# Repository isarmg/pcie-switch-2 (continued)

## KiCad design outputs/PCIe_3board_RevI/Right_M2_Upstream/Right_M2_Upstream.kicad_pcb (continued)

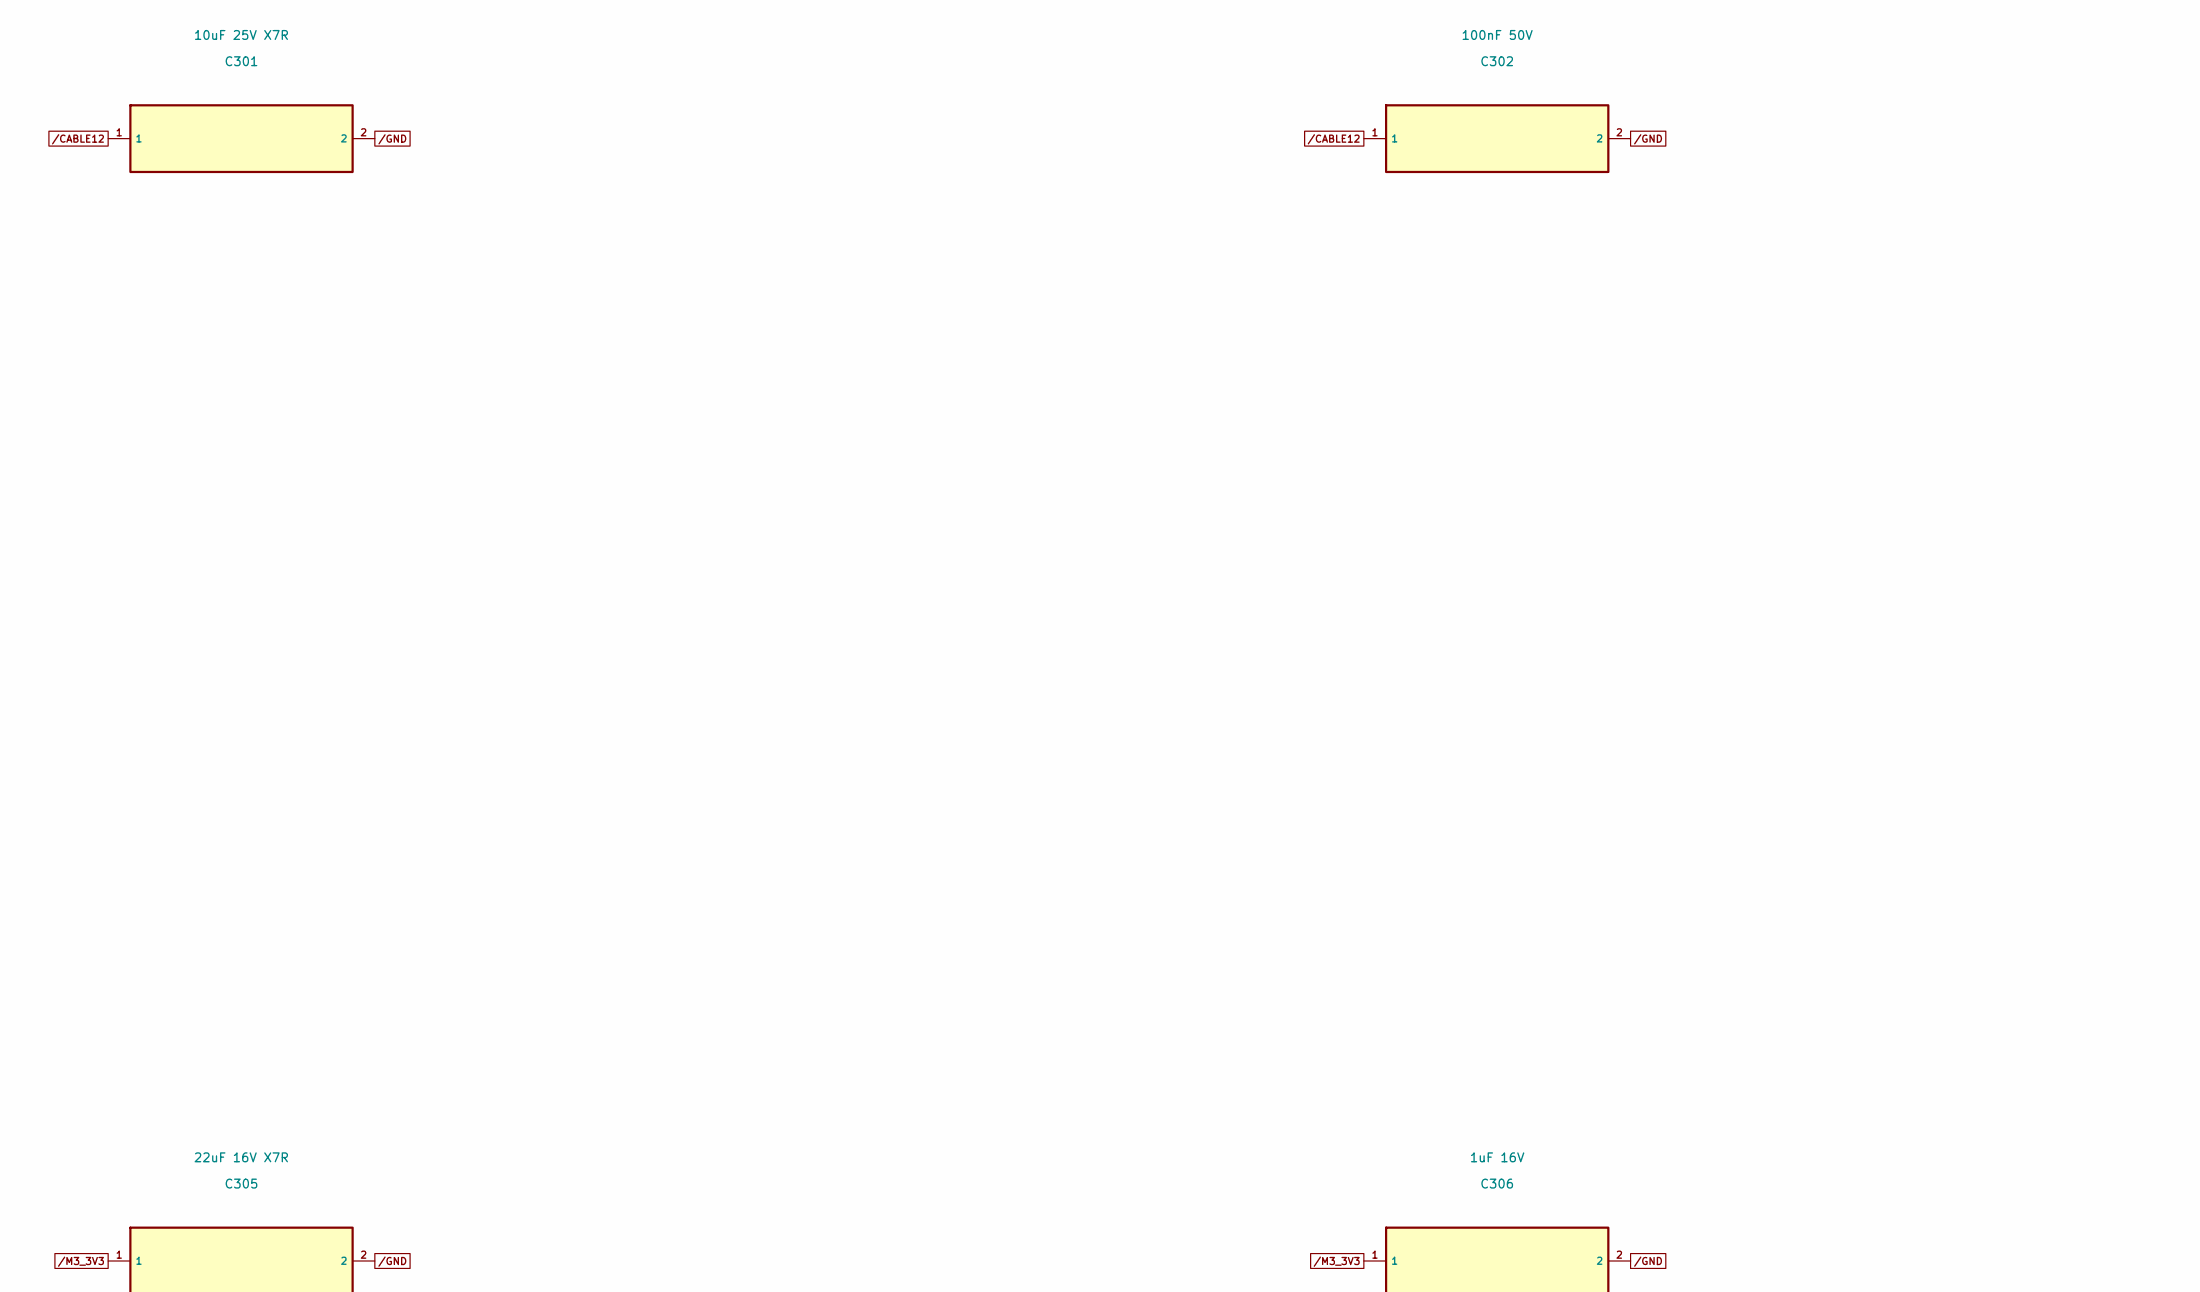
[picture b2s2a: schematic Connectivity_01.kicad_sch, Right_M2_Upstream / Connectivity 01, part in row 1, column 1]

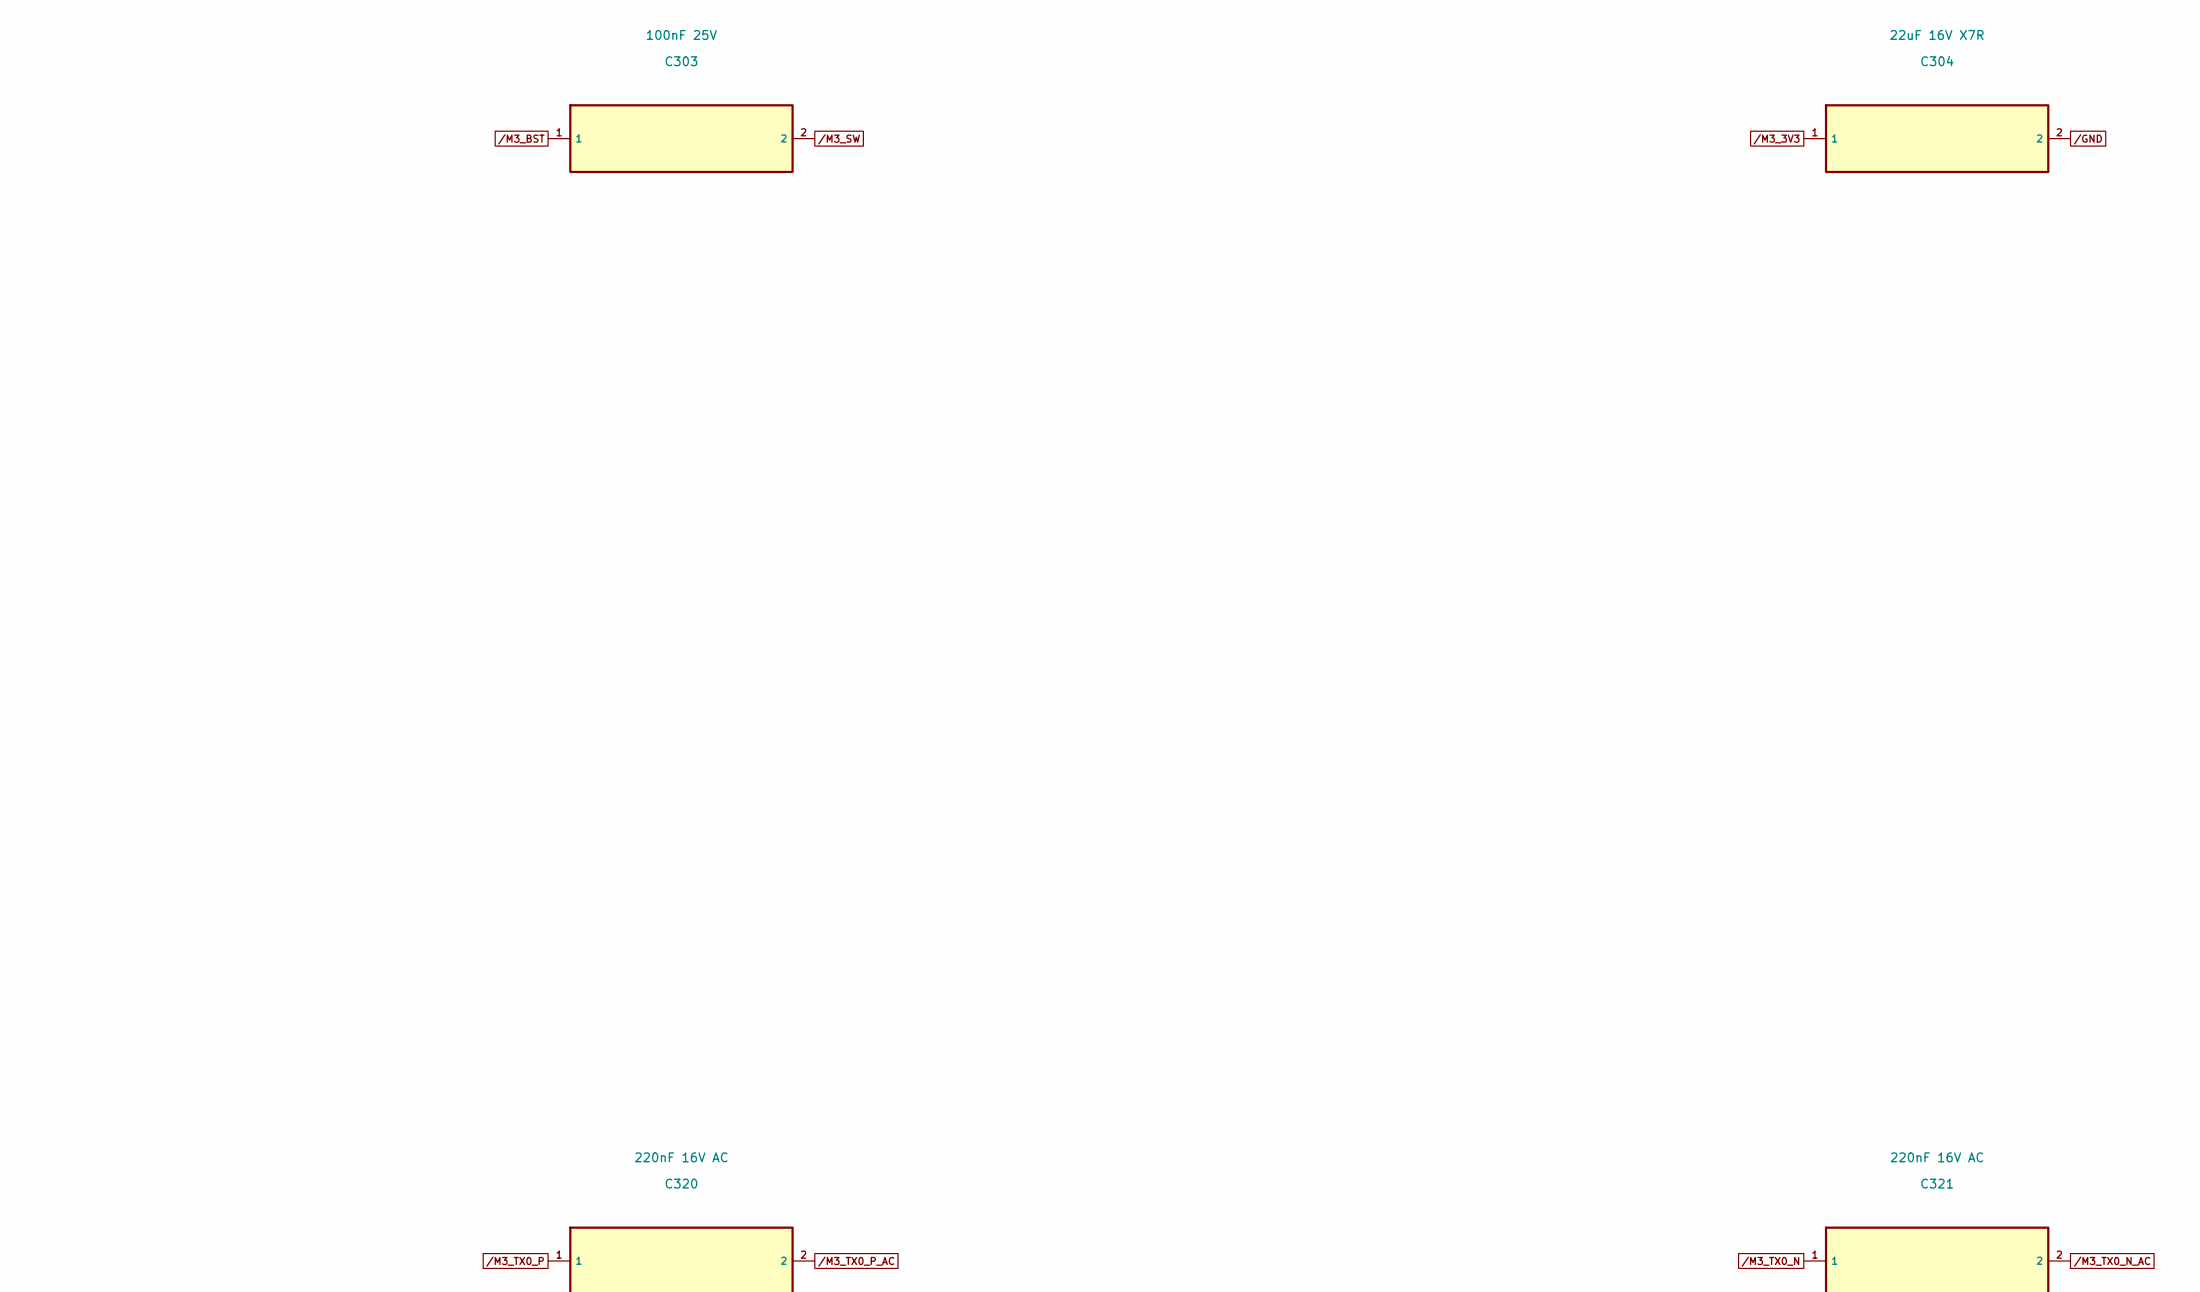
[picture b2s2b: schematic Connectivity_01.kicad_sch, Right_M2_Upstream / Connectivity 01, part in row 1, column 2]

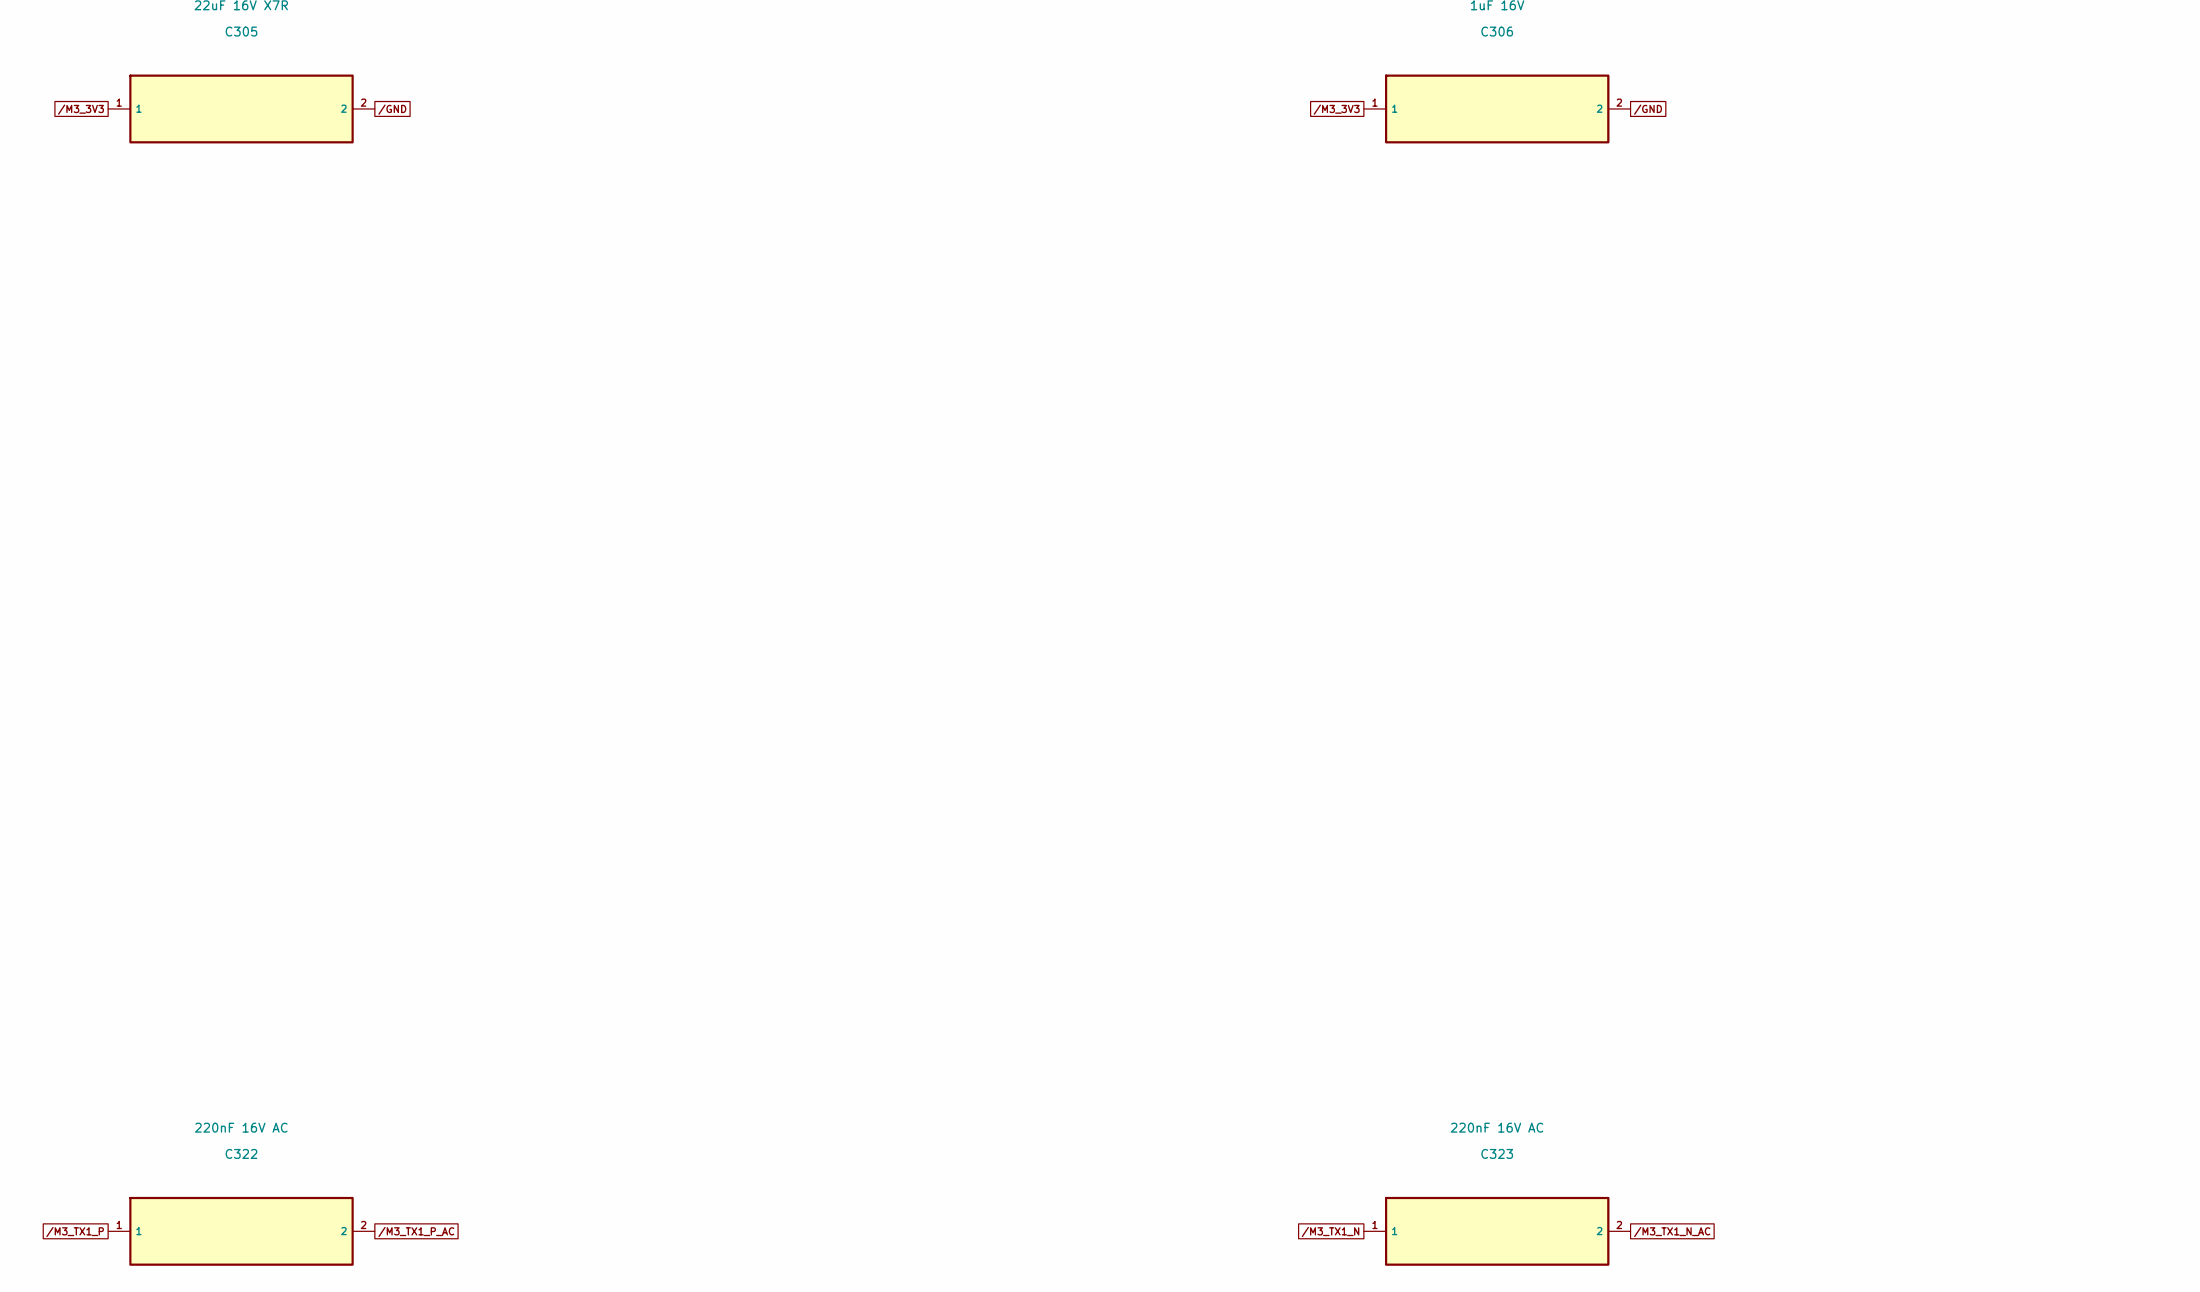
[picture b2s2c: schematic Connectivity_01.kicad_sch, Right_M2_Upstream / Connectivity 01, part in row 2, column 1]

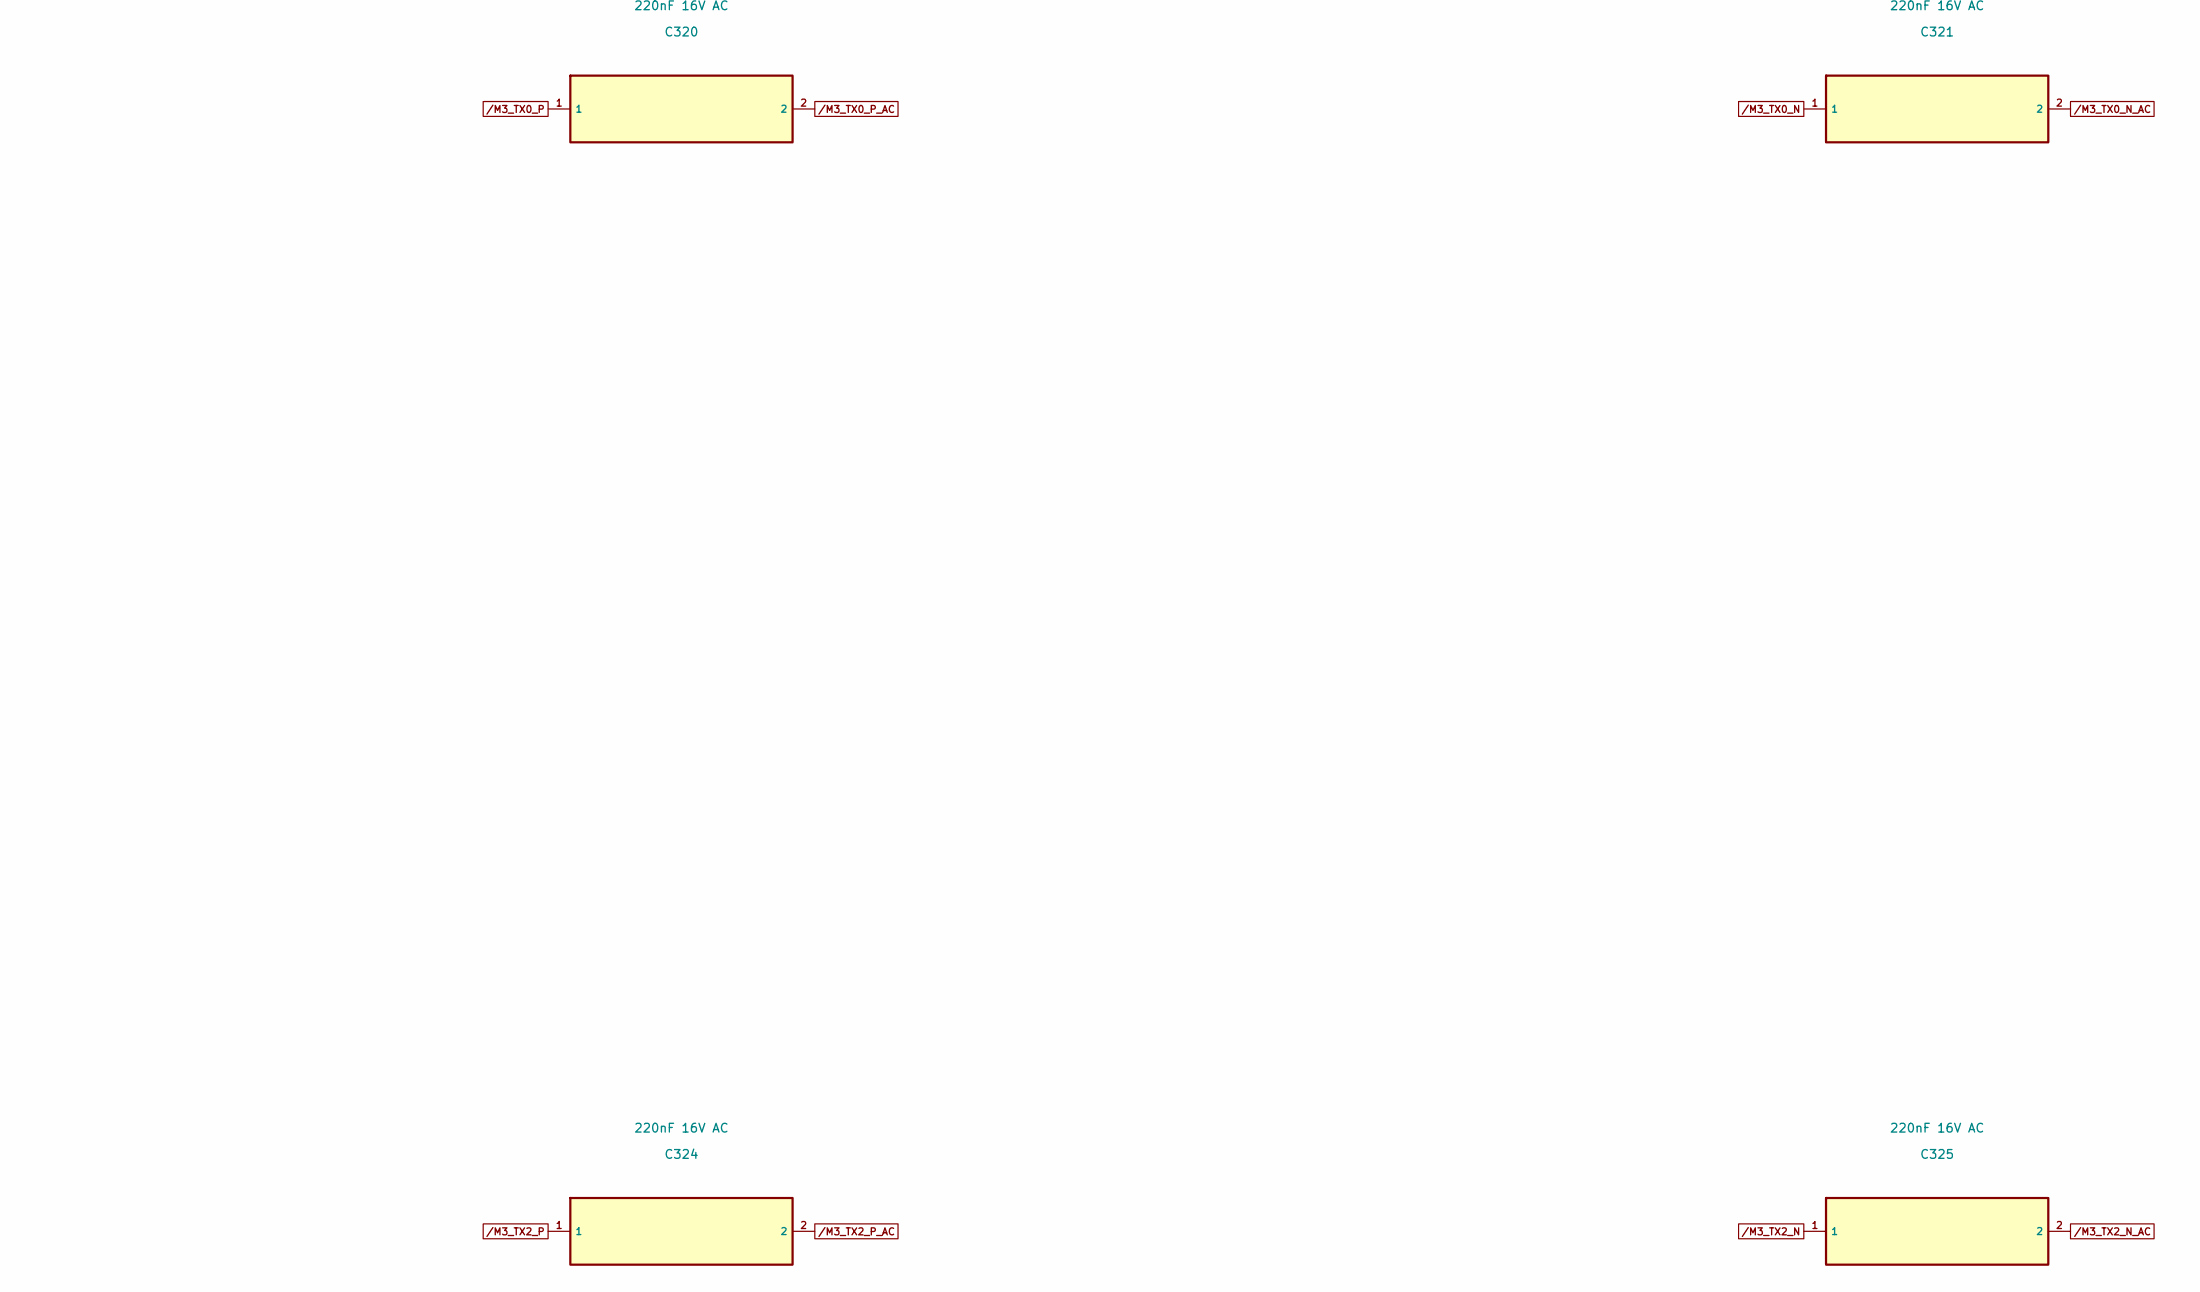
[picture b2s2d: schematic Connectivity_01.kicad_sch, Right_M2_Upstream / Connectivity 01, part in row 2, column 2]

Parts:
C301: 10uF 25V X7R; C_0805_2012Metric
C302: 100nF 50V; C_0402_1005Metric
C303: 100nF 25V; C_0402_1005Metric
C304, C305: 22uF 16V X7R; C_1210_3225Metric
C306: 1uF 16V; C_0603_1608Metric
C320, C321, C322, C323, C324, C325: 220nF 16V AC; C_0402_1005Metric

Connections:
/CABLE12: C301.1, C302.1; also elsewhere on the board
/GND: C301.2, C302.2, C304.2, C305.2, C306.2; also elsewhere on the board
/M3_3V3: C304.1, C305.1, C306.1; also elsewhere on the board
/M3_BST: C303.1; also elsewhere on the board
/M3_SW: C303.2; also elsewhere on the board
/M3_TX0_N: C321.1; also elsewhere on the board
/M3_TX0_N_AC: C321.2; also elsewhere on the board
/M3_TX0_P: C320.1; also elsewhere on the board
/M3_TX0_P_AC: C320.2; also elsewhere on the board
/M3_TX1_N: C323.1; also elsewhere on the board
/M3_TX1_N_AC: C323.2; also elsewhere on the board
/M3_TX1_P: C322.1; also elsewhere on the board
/M3_TX1_P_AC: C322.2; also elsewhere on the board
/M3_TX2_N: C325.1; also elsewhere on the board
/M3_TX2_N_AC: C325.2; also elsewhere on the board
/M3_TX2_P: C324.1; also elsewhere on the board
/M3_TX2_P_AC: C324.2; also elsewhere on the board

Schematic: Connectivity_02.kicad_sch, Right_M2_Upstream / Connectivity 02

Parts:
C326, C327, C420, C421, C422, C423, C424, C425, C426, C427: 220nF 16V AC; C_0402_1005Metric
J3: M-Key 2280 VERTICAL / LAND DRAFT; M2_MKey_VERTICAL_5p3_DRAFT

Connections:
/GND: J3.1 (GND), J3.3 (GND), J3.9 (GND), J3.15 (GND), J3.21 (GND), J3.27 (GND), J3.33 (GND), J3.39 (GND), J3.45 (GND), J3.51 (GND), J3.57 (GND), J3.69 (PEDET), J3.71 (GND), J3.73 (GND), J3.75 (GND), J3.MP1, J3.MP2; also elsewhere on the board
/M3_3V3: J3.2 (3.3V), J3.4 (3.3V), J3.12 (3.3V), J3.14 (3.3V), J3.16 (3.3V), J3.18 (3.3V), J3.70 (3.3V), J3.72 (3.3V), J3.74 (3.3V); also elsewhere on the board
/M3_CLKREQ: J3.52 (~CLKREQ); also elsewhere on the board
/M3_CLK_N: J3.53 (REFCLKn); also elsewhere on the board
/M3_CLK_P: J3.55 (REFCLKp); also elsewhere on the board
/M3_PERST: J3.50 (~PERST); also elsewhere on the board
/M3_RX0_N: J3.41 (PERn0/SATA-B+); also elsewhere on the board
/M3_RX0_P: J3.43 (PERp0/SATA-B-); also elsewhere on the board
/M3_RX1_N: J3.29 (PERn1); also elsewhere on the board
/M3_RX1_P: J3.31 (PERp1); also elsewhere on the board
/M3_RX2_N: J3.17 (PERn2); also elsewhere on the board
/M3_RX2_P: J3.19 (PERp2); also elsewhere on the board
/M3_RX3_N: J3.5 (PERn3); also elsewhere on the board
/M3_RX3_P: J3.7 (PERp3); also elsewhere on the board
/M3_TX0_N_AC: J3.47 (PETn0/SATA-A-); also elsewhere on the board
/M3_TX0_P_AC: J3.49 (PETp0/SATA-A+); also elsewhere on the board
/M3_TX1_N_AC: J3.35 (PETn1); also elsewhere on the board
/M3_TX1_P_AC: J3.37 (PETp1); also elsewhere on the board
/M3_TX2_N_AC: J3.23 (PETn2); also elsewhere on the board
/M3_TX2_P_AC: J3.25 (PETp2); also elsewhere on the board
/M3_TX3_N: C327.1; also elsewhere on the board
/M3_TX3_N_AC: C327.2, J3.11 (PETn3)
/M3_TX3_P: C326.1; also elsewhere on the board
/M3_TX3_P_AC: C326.2, J3.13 (PETp3)
/M3_WAKE: J3.54 (~PEWAKE); also elsewhere on the board
/UP_TX0_N: C421.1; also elsewhere on the board
/UP_TX0_N_AC: C421.2; also elsewhere on the board
/UP_TX0_P: C420.1; also elsewhere on the board
/UP_TX0_P_AC: C420.2; also elsewhere on the board
/UP_TX1_N: C423.1; also elsewhere on the board
/UP_TX1_N_AC: C423.2; also elsewhere on the board
/UP_TX1_P: C422.1; also elsewhere on the board
/UP_TX1_P_AC: C422.2; also elsewhere on the board
/UP_TX2_N: C425.1; also elsewhere on the board
/UP_TX2_N_AC: C425.2; also elsewhere on the board
/UP_TX2_P: C424.1; also elsewhere on the board
/UP_TX2_P_AC: C424.2; also elsewhere on the board
/UP_TX3_N: C427.1; also elsewhere on the board
/UP_TX3_N_AC: C427.2; also elsewhere on the board
/UP_TX3_P: C426.1; also elsewhere on the board
/UP_TX3_P_AC: C426.2; also elsewhere on the board

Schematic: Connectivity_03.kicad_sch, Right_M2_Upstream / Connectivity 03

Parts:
J4: UPLINK M-Key / HOST ONLY; M2_MKey_VERTICAL_5p3_DRAFT
J50: 12V protected / GND; Wire_12V_GND_3A
J51: Control / custom; Control_8_Wire
J101: M3 TX0; Twinax_85R_Solder_DRAFT
J102: M3 RX0; Twinax_85R_Solder_DRAFT
J103: M3 TX1; Twinax_85R_Solder_DRAFT
J104: M3 RX1; Twinax_85R_Solder_DRAFT
J105: M3 TX2; Twinax_85R_Solder_DRAFT
J106: M3 RX2; Twinax_85R_Solder_DRAFT
J107: M3 TX3; Twinax_85R_Solder_DRAFT
J108: M3 RX3; Twinax_85R_Solder_DRAFT

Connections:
/CABLE12: J50.1; also elsewhere on the board
/GND: J4.1 (GND), J4.3 (GND), J4.9 (GND), J4.15 (GND), J4.21 (GND), J4.27 (GND), J4.33 (GND), J4.39 (GND), J4.45 (GND), J4.51 (GND), J4.57 (GND), J4.69 (PEDET), J4.71 (GND), J4.73 (GND), J4.75 (GND), J4.MP1, J4.MP2, J50.2, J51.7, J51.8, J101.G, J102.G, J103.G, J104.G, J105.G, J106.G, J107.G, J108.G; also elsewhere on the board
/M3_CLKREQ: J51.2; also elsewhere on the board
/M3_PERST: J51.1; also elsewhere on the board
/M3_RX0_N: J102.N; also elsewhere on the board
/M3_RX0_P: J102.P; also elsewhere on the board
/M3_RX1_N: J104.N; also elsewhere on the board
/M3_RX1_P: J104.P; also elsewhere on the board
/M3_RX2_N: J106.N; also elsewhere on the board
/M3_RX2_P: J106.P; also elsewhere on the board
/M3_RX3_N: J108.N; also elsewhere on the board
/M3_RX3_P: J108.P; also elsewhere on the board
/M3_TX0_N: J101.N; also elsewhere on the board
/M3_TX0_P: J101.P; also elsewhere on the board
/M3_TX1_N: J103.N; also elsewhere on the board
/M3_TX1_P: J103.P; also elsewhere on the board
/M3_TX2_N: J105.N; also elsewhere on the board
/M3_TX2_P: J105.P; also elsewhere on the board
/M3_TX3_N: J107.N; also elsewhere on the board
/M3_TX3_P: J107.P; also elsewhere on the board
/M3_WAKE: J51.3; also elsewhere on the board
/UP_CLKREQ: J4.52 (~CLKREQ), J51.5; also elsewhere on the board
/UP_CLK_N: J4.53 (REFCLKn); also elsewhere on the board
/UP_CLK_P: J4.55 (REFCLKp); also elsewhere on the board
/UP_PERST: J4.50 (~PERST), J51.4
/UP_RX0_N: J4.47 (PETn0/SATA-A-); also elsewhere on the board
/UP_RX0_P: J4.49 (PETp0/SATA-A+); also elsewhere on the board
/UP_RX1_N: J4.35 (PETn1); also elsewhere on the board
/UP_RX1_P: J4.37 (PETp1); also elsewhere on the board
/UP_RX2_N: J4.23 (PETn2); also elsewhere on the board
/UP_RX2_P: J4.25 (PETp2); also elsewhere on the board
/UP_RX3_N: J4.11 (PETn3); also elsewhere on the board
/UP_RX3_P: J4.13 (PETp3); also elsewhere on the board
/UP_TX0_N_AC: J4.41 (PERn0/SATA-B+); also elsewhere on the board
/UP_TX0_P_AC: J4.43 (PERp0/SATA-B-); also elsewhere on the board
/UP_TX1_N_AC: J4.29 (PERn1); also elsewhere on the board
/UP_TX1_P_AC: J4.31 (PERp1); also elsewhere on the board
/UP_TX2_N_AC: J4.17 (PERn2); also elsewhere on the board
/UP_TX2_P_AC: J4.19 (PERp2); also elsewhere on the board
/UP_TX3_N_AC: J4.5 (PERn3); also elsewhere on the board
/UP_TX3_P_AC: J4.7 (PERp3); also elsewhere on the board
/UP_WAKE: J4.54 (~PEWAKE), J51.6

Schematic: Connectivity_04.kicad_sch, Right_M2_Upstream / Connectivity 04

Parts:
J109: M3 CLK; Twinax_85R_Solder_DRAFT
J110: UP TX0; Twinax_85R_Solder_DRAFT
J111: UP RX0; Twinax_85R_Solder_DRAFT
J112: UP TX1; Twinax_85R_Solder_DRAFT
J113: UP RX1; Twinax_85R_Solder_DRAFT
J114: UP TX2; Twinax_85R_Solder_DRAFT
J115: UP RX2; Twinax_85R_Solder_DRAFT
J116: UP TX3; Twinax_85R_Solder_DRAFT
J117: UP RX3; Twinax_85R_Solder_DRAFT
J118: UP CLK; Twinax_85R_Solder_DRAFT
L3: 2.2uH XAL5030-222MEC; L_Coilcraft_XAL5030-XXX
R301: 33.2k; R_0402_1005Metric

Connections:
/GND: J109.G, J110.G, J111.G, J112.G, J113.G, J114.G, J115.G, J116.G, J117.G, J118.G; also elsewhere on the board
/M3_3V3: L3.2, R301.1; also elsewhere on the board
/M3_CLK_N: J109.N; also elsewhere on the board
/M3_CLK_P: J109.P; also elsewhere on the board
/M3_FB: R301.2; also elsewhere on the board
/M3_SW: L3.1; also elsewhere on the board
/UP_CLK_N: J118.N; also elsewhere on the board
/UP_CLK_P: J118.P; also elsewhere on the board
/UP_RX0_N: J111.N; also elsewhere on the board
/UP_RX0_P: J111.P; also elsewhere on the board
/UP_RX1_N: J113.N; also elsewhere on the board
/UP_RX1_P: J113.P; also elsewhere on the board
/UP_RX2_N: J115.N; also elsewhere on the board
/UP_RX2_P: J115.P; also elsewhere on the board
/UP_RX3_N: J117.N; also elsewhere on the board
/UP_RX3_P: J117.P; also elsewhere on the board
/UP_TX0_N: J110.N; also elsewhere on the board
/UP_TX0_P: J110.P; also elsewhere on the board
/UP_TX1_N: J112.N; also elsewhere on the board
/UP_TX1_P: J112.P; also elsewhere on the board
/UP_TX2_N: J114.N; also elsewhere on the board
/UP_TX2_P: J114.P; also elsewhere on the board
/UP_TX3_N: J116.N; also elsewhere on the board
/UP_TX3_P: J116.P; also elsewhere on the board

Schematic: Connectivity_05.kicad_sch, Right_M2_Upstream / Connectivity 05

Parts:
R302, R310, R311: 10k; R_0402_1005Metric
TP1: UP CLKREQ reserved; Testpad_1
U23: TPS565201DDCR; SOT-23-6

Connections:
/CABLE12: U23.3 (VIN), U23.5 (EN); also elsewhere on the board
/GND: R302.2, U23.1 (GND); also elsewhere on the board
/M3_3V3: R310.1, R311.1; also elsewhere on the board
/M3_BST: U23.6 (VBST); also elsewhere on the board
/M3_CLKREQ: R310.2; also elsewhere on the board
/M3_FB: R302.1, U23.4 (VFB); also elsewhere on the board
/M3_SW: U23.2 (SW); also elsewhere on the board
/M3_WAKE: R311.2; also elsewhere on the board
/UP_CLKREQ: TP1.1; also elsewhere on the board

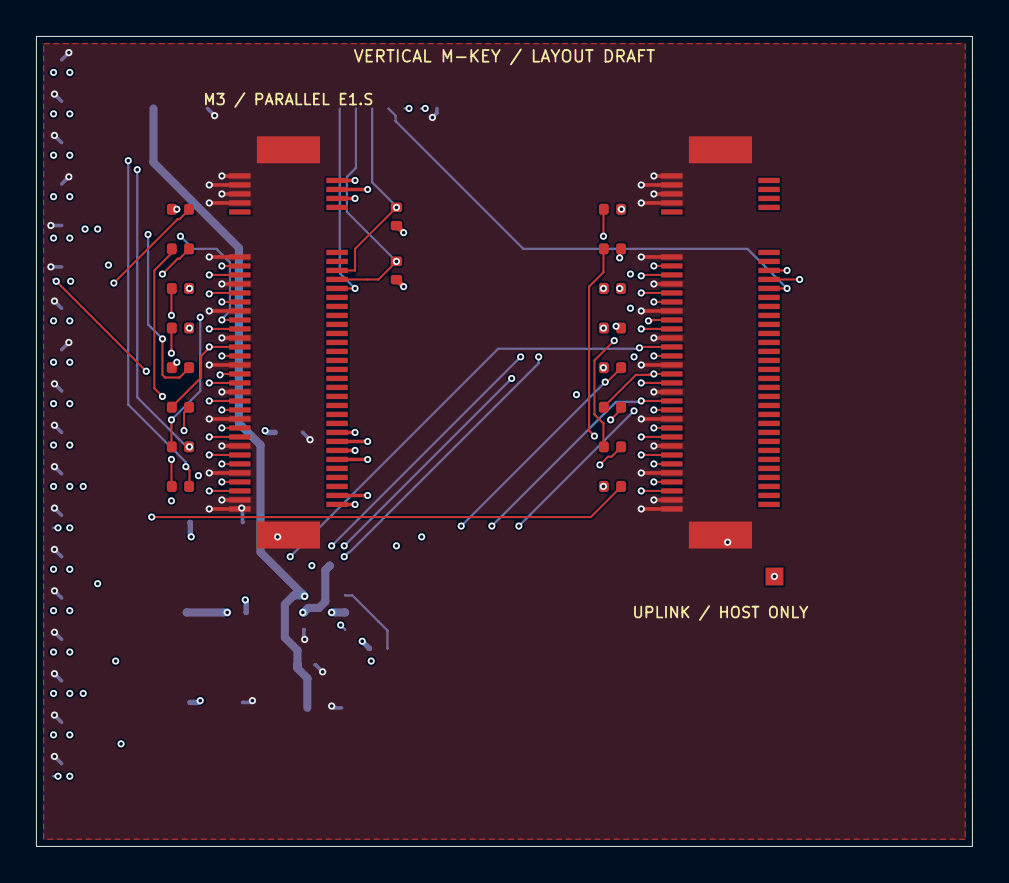
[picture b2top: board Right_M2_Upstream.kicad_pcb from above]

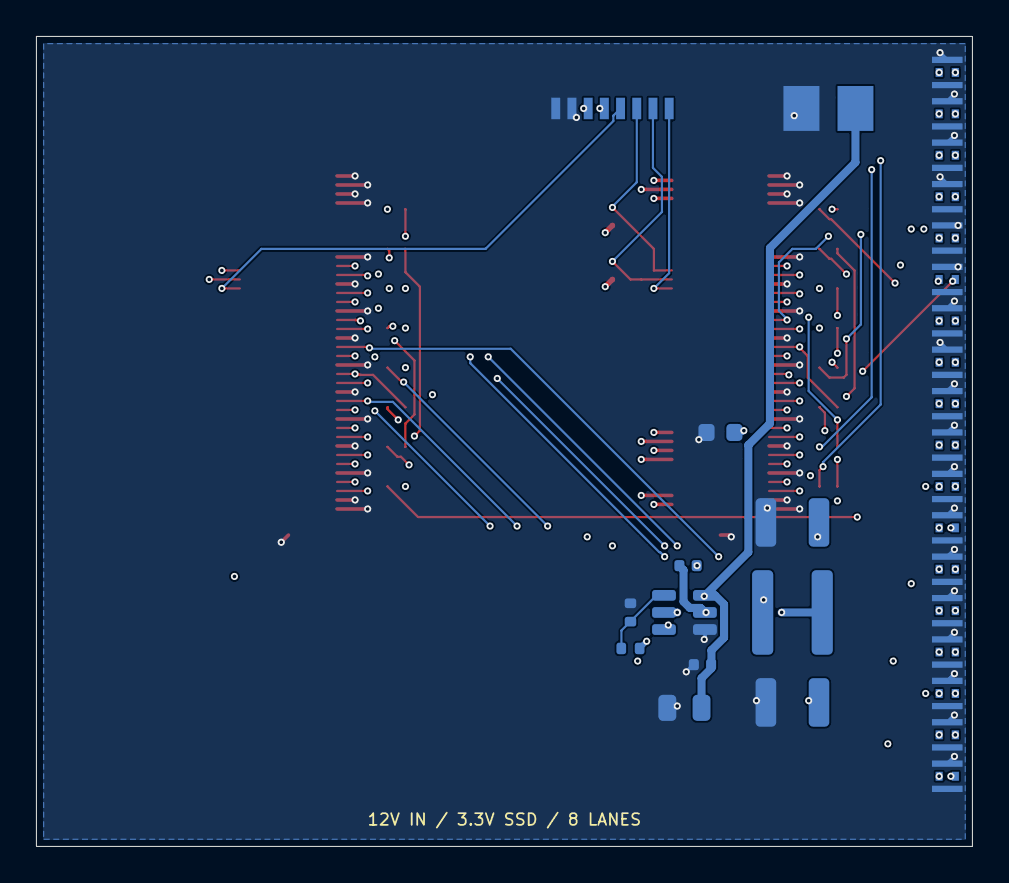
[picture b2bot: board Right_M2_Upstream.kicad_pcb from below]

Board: 12 copper layers, 52.0 x 45.0 mm, 51 parts (30 on the bottom side), 64 nets.

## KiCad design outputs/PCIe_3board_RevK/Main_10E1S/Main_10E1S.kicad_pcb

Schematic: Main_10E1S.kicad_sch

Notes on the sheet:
REV K: UNROUTED PLACEMENT / NET-ASSIGNMENT DRAFT Main routing pending. Intel parts are mechanical reservations, with no verified ball maps. Pin types are passive: ERC does not validate power sequencing, firmware, or link behavior. See README.md and VALIDATION.json before manufacturing.
